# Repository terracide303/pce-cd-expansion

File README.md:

# PC Engine CD-ROM² card

> **Beta.** The PCB design is done, nothing has been built or tested yet. The FPGA core
> is still in development and will not be public until it is done.

A HuCard-sized card for the PC Engine / TurboGrafx-16. It plugs into the
**HuCard slot** and emulates the CD-ROM² system from a microSD card. No
expansion-port hardware and no CD unit are needed.

## On the card

- Lattice ECP5-45F FPGA with SDRAM and config flash (core section after the Icepi Zero)
- RP2040 companion and microSD
- Two USB-C ports: FPGA programming (FT231X) and the RP2040
- PCM5102A audio DAC: a stereo 3.5 mm jack, plus mono to the console
- 5 V bus translators at the card edge
- 4 layers, 54.1 × 85.4 mm, 1.6 mm, ENIG gold fingers

## Status

| part | state |
|---|---|
| schematic | done, checked |
| PCB | done, beta |
| FPGA core | in development, not public yet |
| ordered / tested | no |

## Layout

- `hw/card/`: KiCad project
- `tools/`: scripts that generate, check and lay out the board, and make the fab files
- `docs/`: [the card](docs/CARD.md), [how it is built](docs/WORKFLOW.md), [ordering](docs/ORDER.md); old notes in `docs/archive/`

## Credits

- [Icepi Zero](https://github.com/cheyao/icepi-zero) (Solderpad 2.1): the FPGA core section of the board
- [MiSTer TurboGrafx-16 core](https://github.com/MiSTer-devel/TurboGrafx16_MiSTer): reference for the CD hardware
- [HuCARD-repro](https://github.com/partlyhuman/HuCARD-repro): HuCard dimensions

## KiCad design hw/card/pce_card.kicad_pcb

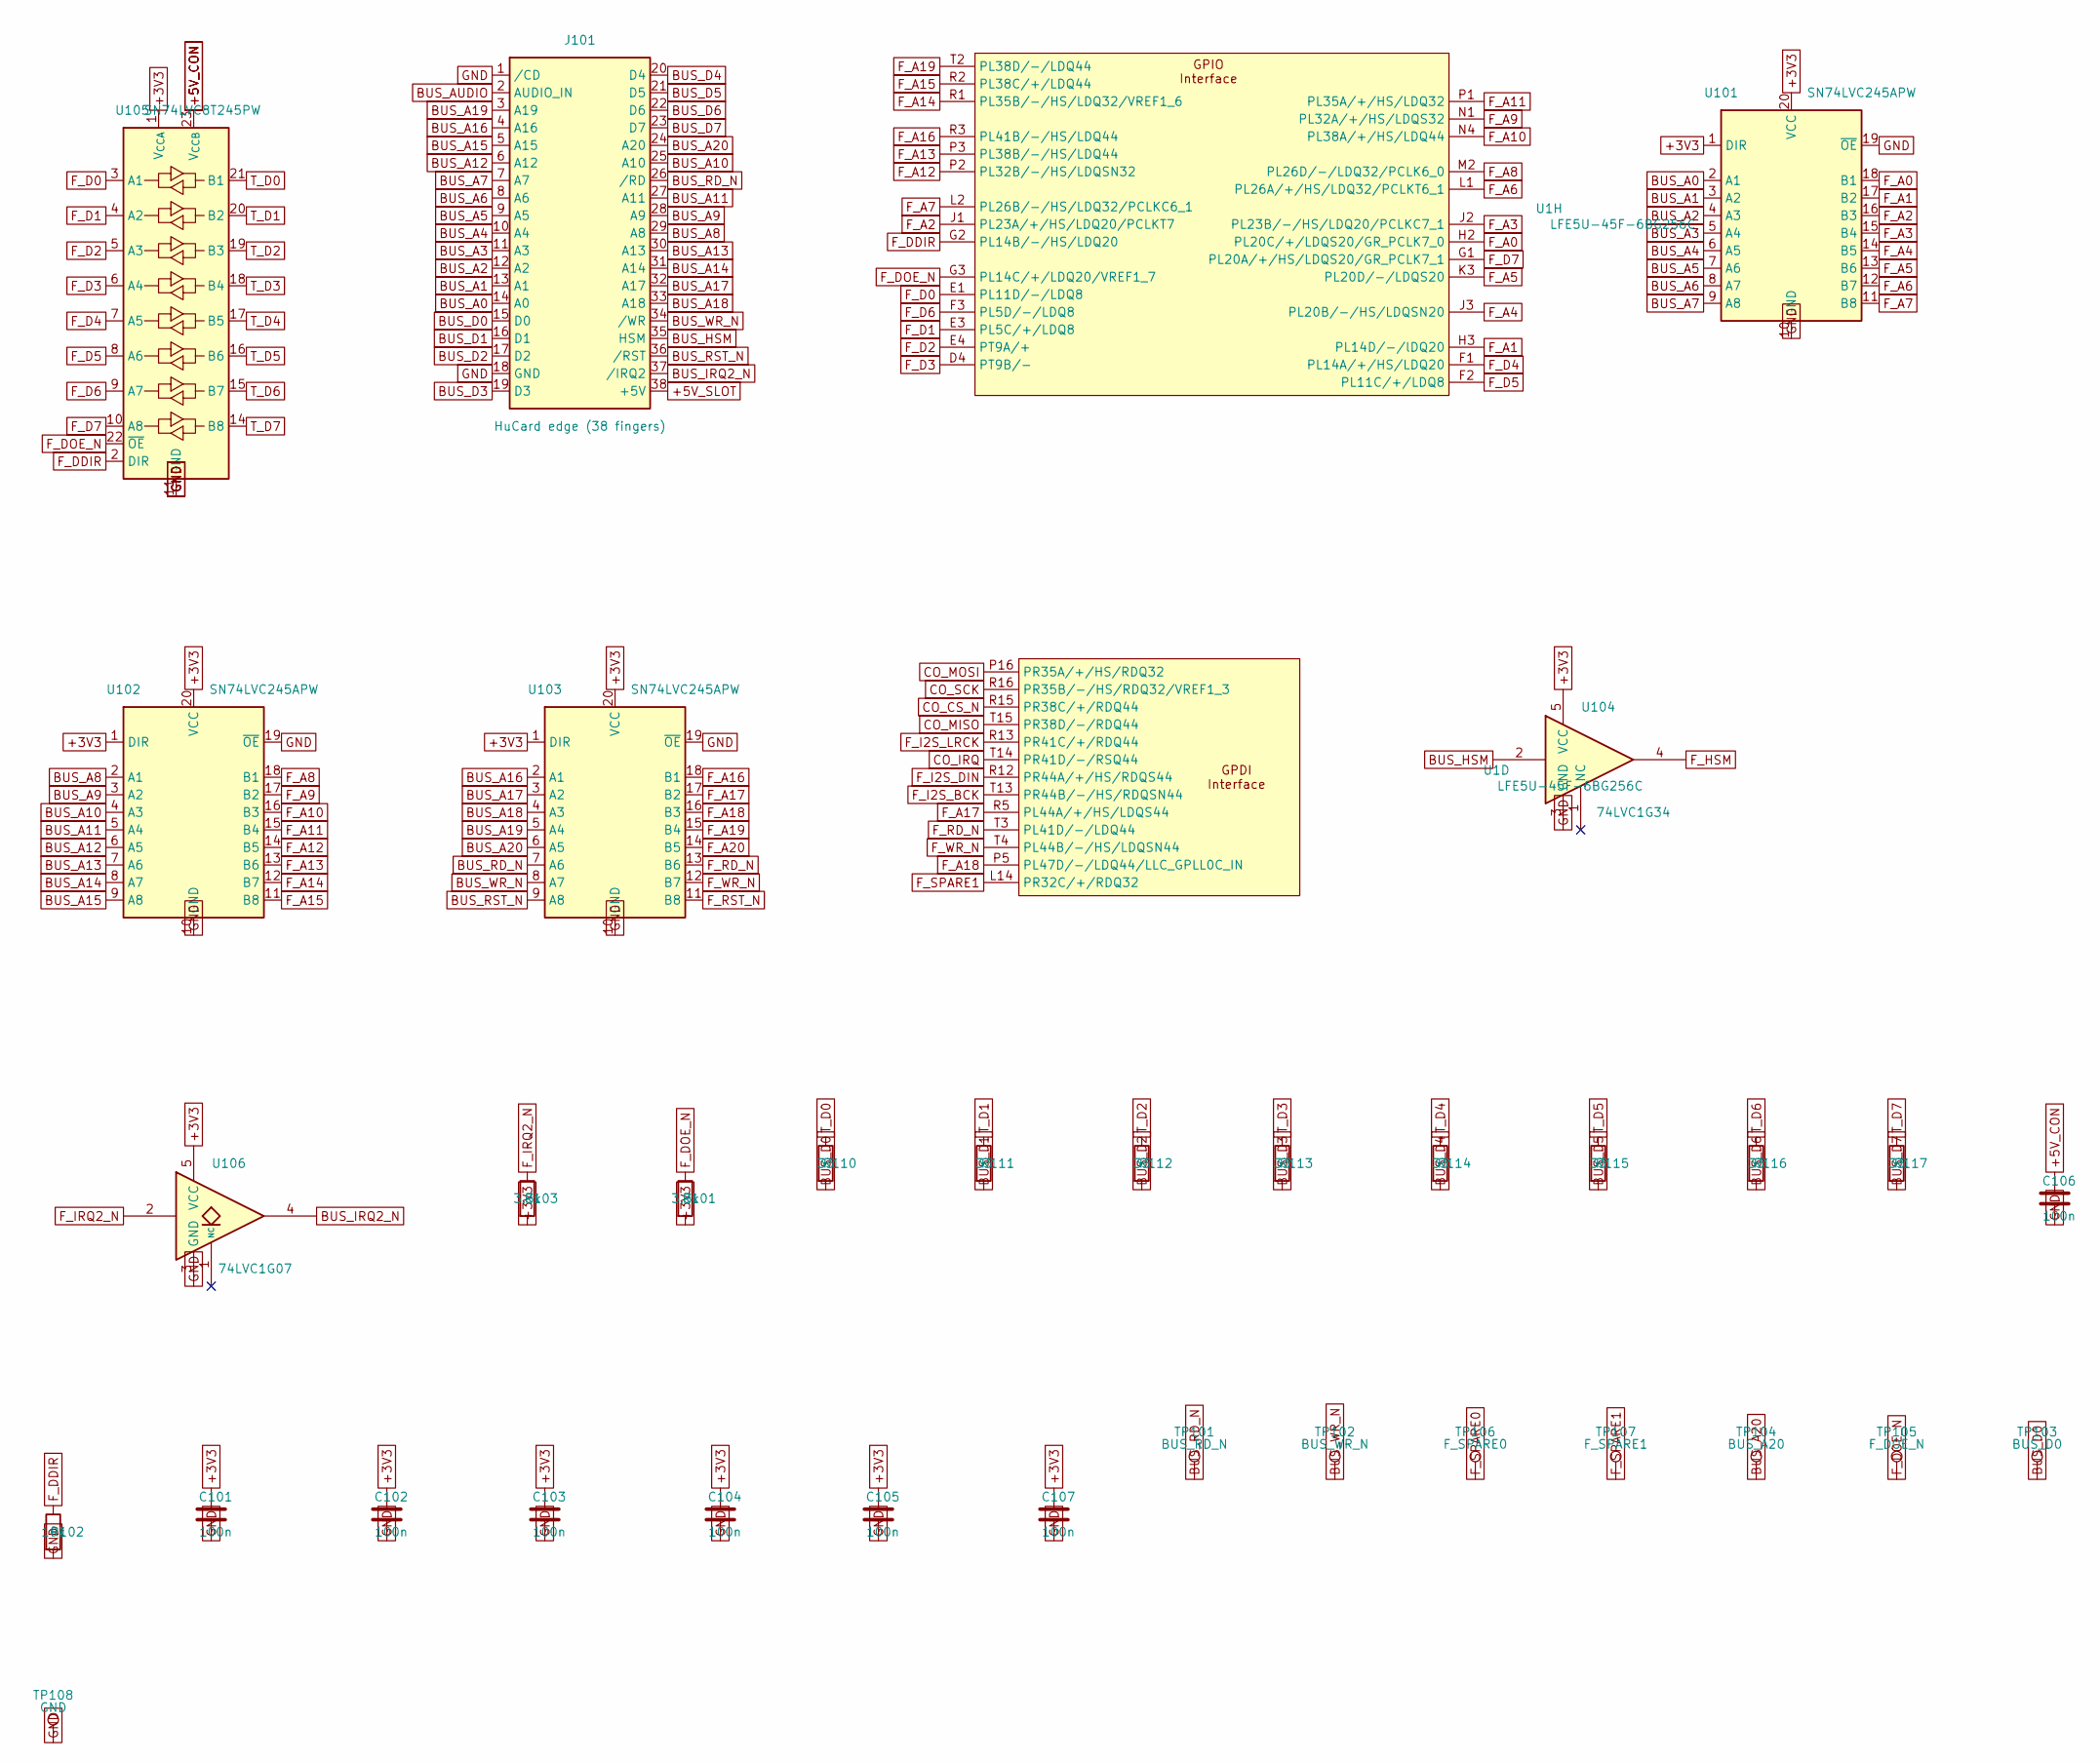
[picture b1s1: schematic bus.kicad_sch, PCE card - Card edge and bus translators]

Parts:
C101, C102, C103, C104, C105, C106, C107: 100n; C_0402_1005Metric; LCSC C307331
J101: HuCard edge (38 fingers); HuCard_Edge_38
R101, R103: 3.3k; R_0402_1005Metric; LCSC C25890
R102: 10k; R_0402_1005Metric; LCSC C25744
R110, R111, R112, R113, R114, R115, R116, R117: 33; R_0402_1005Metric
TP101: BUS_RD_N; TestPoint_Pad_D1.0mm
TP102: BUS_WR_N; TestPoint_Pad_D1.0mm
TP103: BUS_D0; TestPoint_Pad_D1.0mm
TP104: BUS_A20; TestPoint_Pad_D1.0mm
TP105: F_DOE_N; TestPoint_Pad_D1.0mm
TP106: F_SPARE0; TestPoint_Pad_D1.0mm
TP107: F_SPARE1; TestPoint_Pad_D1.0mm
TP108: GND; TestPoint_Pad_D1.0mm
U1: LFE5U-45F-6BG256C; BGA-256_14.0x14.0mm_Layout16x16_P0.8mm_Ball0.45mm_Pad0.32mm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; LCSC C1550834
U101, U102, U103: SN74LVC245APW; TSSOP-20_4.4x6.5mm_P0.65mm
U104: 74LVC1G34; SOT-23-5
U105: SN74LVC8T245PW; TSSOP-24_4.4x7.8mm_P0.65mm
U106: 74LVC1G07; SOT-23-5

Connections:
+3V3: C101.1, C102.1, C103.1, C104.1, C105.1, C107.1, R101.2, R103.2, U101.1 (DIR), U101.20 (VCC), U102.1 (DIR), U102.20 (VCC), U103.1 (DIR), U103.20 (VCC), U104.5 (VCC), U105.1 (V_{CCA}), U106.5 (VCC); also elsewhere on the board
+5V_CON: C106.1, U105.23 (V_{CCB}), U105.24 (V_{CCB}); also elsewhere on the board
+5V_SLOT: J101.38 (+5V); also elsewhere on the board
BUS_A0: J101.14 (A0), U101.2 (A1)
BUS_A1: J101.13 (A1), U101.3 (A2)
BUS_A2: J101.12 (A2), U101.4 (A3)
BUS_A3: J101.11 (A3), U101.5 (A4)
BUS_A4: J101.10 (A4), U101.6 (A5)
BUS_A5: J101.9 (A5), U101.7 (A6)
BUS_A6: J101.8 (A6), U101.8 (A7)
BUS_A7: J101.7 (A7), U101.9 (A8)
BUS_A8: J101.29 (A8), U102.2 (A1)
BUS_A9: J101.28 (A9), U102.3 (A2)
BUS_A10: J101.25 (A10), U102.4 (A3)
BUS_A11: J101.27 (A11), U102.5 (A4)
BUS_A12: J101.6 (A12), U102.6 (A5)
BUS_A13: J101.30 (A13), U102.7 (A6)
BUS_A14: J101.31 (A14), U102.8 (A7)
BUS_A15: J101.5 (A15), U102.9 (A8)
BUS_A16: J101.4 (A16), U103.2 (A1)
BUS_A17: J101.32 (A17), U103.3 (A2)
BUS_A18: J101.33 (A18), U103.4 (A3)
BUS_A19: J101.3 (A19), U103.5 (A4)
BUS_A20: J101.24 (A20), TP104.1, U103.6 (A5)
BUS_AUDIO: J101.2 (AUDIO_IN); also elsewhere on the board
BUS_D0: J101.15 (D0), R110.2, TP103.1
BUS_D1: J101.16 (D1), R111.2
BUS_D2: J101.17 (D2), R112.2
BUS_D3: J101.19 (D3), R113.2
BUS_D4: J101.20 (D4), R114.2
BUS_D5: J101.21 (D5), R115.2
BUS_D6: J101.22 (D6), R116.2
BUS_D7: J101.23 (D7), R117.2
BUS_HSM: J101.35 (HSM), U104.2
BUS_IRQ2_N: J101.37 (/IRQ2), U106.4
BUS_RD_N: J101.26 (/RD), TP101.1, U103.7 (A6)
BUS_RST_N: J101.36 (/RST), U103.9 (A8)
BUS_WR_N: J101.34 (/WR), TP102.1, U103.8 (A7)
CO_CS_N: U1.R15 (PR38C/+/RDQ44); also elsewhere on the board
CO_IRQ: U1.T14 (PR41D/-/RSQ44); also elsewhere on the board
CO_MISO: U1.T15 (PR38D/-/RDQ44); also elsewhere on the board
CO_MOSI: U1.P16 (PR35A/+/HS/RDQ32); also elsewhere on the board
CO_SCK: U1.R16 (PR35B/-/HS/RDQ32/VREF1_3); also elsewhere on the board
F_A0: U1.H2 (PL20C/+/LDQS20/GR_PCLK7_0), U101.18 (B1)
F_A1: U1.H3 (PL14D/-/lDQ20), U101.17 (B2)
F_A2: U1.J1 (PL23A/+/HS/LDQ20/PCLKT7), U101.16 (B3)
F_A3: U1.J2 (PL23B/-/HS/LDQ20/PCLKC7_1), U101.15 (B4)
F_A4: U1.J3 (PL20B/-/HS/LDQSN20), U101.14 (B5)
F_A5: U1.K3 (PL20D/-/LDQS20), U101.13 (B6)
F_A6: U1.L1 (PL26A/+/HS/LDQ32/PCLKT6_1), U101.12 (B7)
F_A7: U1.L2 (PL26B/-/HS/LDQ32/PCLKC6_1), U101.11 (B8)
F_A8: U1.M2 (PL26D/-/LDQ32/PCLK6_0), U102.18 (B1)
F_A9: U1.N1 (PL32A/+/HS/LDQS32), U102.17 (B2)
F_A10: U1.N4 (PL38A/+/HS/LDQ44), U102.16 (B3)
F_A11: U1.P1 (PL35A/+/HS/LDQ32), U102.15 (B4)
F_A12: U1.P2 (PL32B/-/HS/LDQSN32), U102.14 (B5)
F_A13: U1.P3 (PL38B/-/HS/LDQ44), U102.13 (B6)
F_A14: U1.R1 (PL35B/-/HS/LDQ32/VREF1_6), U102.12 (B7)
F_A15: U1.R2 (PL38C/+/LDQ44), U102.11 (B8)
F_A16: U1.R3 (PL41B/-/HS/LDQ44), U103.18 (B1)
F_A17: U1.R5 (PL44A/+/HS/LDQS44), U103.17 (B2)
F_A18: U1.P5 (PL47D/-/LDQ44/LLC_GPLL0C_IN), U103.16 (B3)
F_A19: U1.T2 (PL38D/-/LDQ44), U103.15 (B4)
F_A20: U103.14 (B5); also elsewhere on the board
F_D0: U1.E1 (PL11D/-/LDQ8), U105.3 (A1)
F_D1: U1.E3 (PL5C/+/LDQ8), U105.4 (A2)
F_D2: U1.E4 (PT9A/+), U105.5 (A3)
F_D3: U1.D4 (PT9B/-), U105.6 (A4)
F_D4: U1.F1 (PL14A/+/HS/LDQ20), U105.7 (A5)
F_D5: U1.F2 (PL11C/+/LDQ8), U105.8 (A6)
F_D6: U1.F3 (PL5D/-/LDQ8), U105.9 (A7)
F_D7: U1.G1 (PL20A/+/HS/LDQS20/GR_PCLK7_1), U105.10 (A8)
F_DDIR: R102.1, U1.G2 (PL14B/-/HS/LDQ20), U105.2 (DIR)
F_DOE_N: R101.1, TP105.1, U1.G3 (PL14C/+/LDQ20/VREF1_7), U105.22 (~OE)
F_HSM: U104.4; also elsewhere on the board
F_I2S_BCK: U1.T13 (PR44B/-/HS/RDQSN44); also elsewhere on the board
F_I2S_DIN: U1.R12 (PR44A/+/HS/RDQS44); also elsewhere on the board
F_I2S_LRCK: U1.R13 (PR41C/+/RDQ44); also elsewhere on the board
F_IRQ2_N: R103.1, U106.2; also elsewhere on the board
F_RD_N: U1.T3 (PL41D/-/LDQ44), U103.13 (B6)
F_RST_N: U103.11 (B8); also elsewhere on the board
F_SPARE0: TP106.1; also elsewhere on the board
F_SPARE1: TP107.1, U1.L14 (PR32C/+/RDQ32)
F_WR_N: U1.T4 (PL44B/-/HS/LDQSN44), U103.12 (B7)
GND: C101.2, C102.2, C103.2, C104.2, C105.2, C106.2, C107.2, J101.1 (/CD), J101.18 (GND), R102.2, TP108.1, U101.10 (GND), U101.19 (~OE), U102.10 (GND), U102.19 (~OE), U103.10 (GND), U103.19 (~OE), U104.3 (GND), U105.11 (GND), U105.12 (GND), U105.13 (GND), U106.3 (GND); also elsewhere on the board
T_D0: R110.1, U105.21 (B1)
T_D1: R111.1, U105.20 (B2)
T_D2: R112.1, U105.19 (B3)
T_D3: R113.1, U105.18 (B4)
T_D4: R114.1, U105.17 (B5)
T_D5: R115.1, U105.16 (B6)
T_D6: R116.1, U105.15 (B7)
T_D7: R117.1, U105.14 (B8)

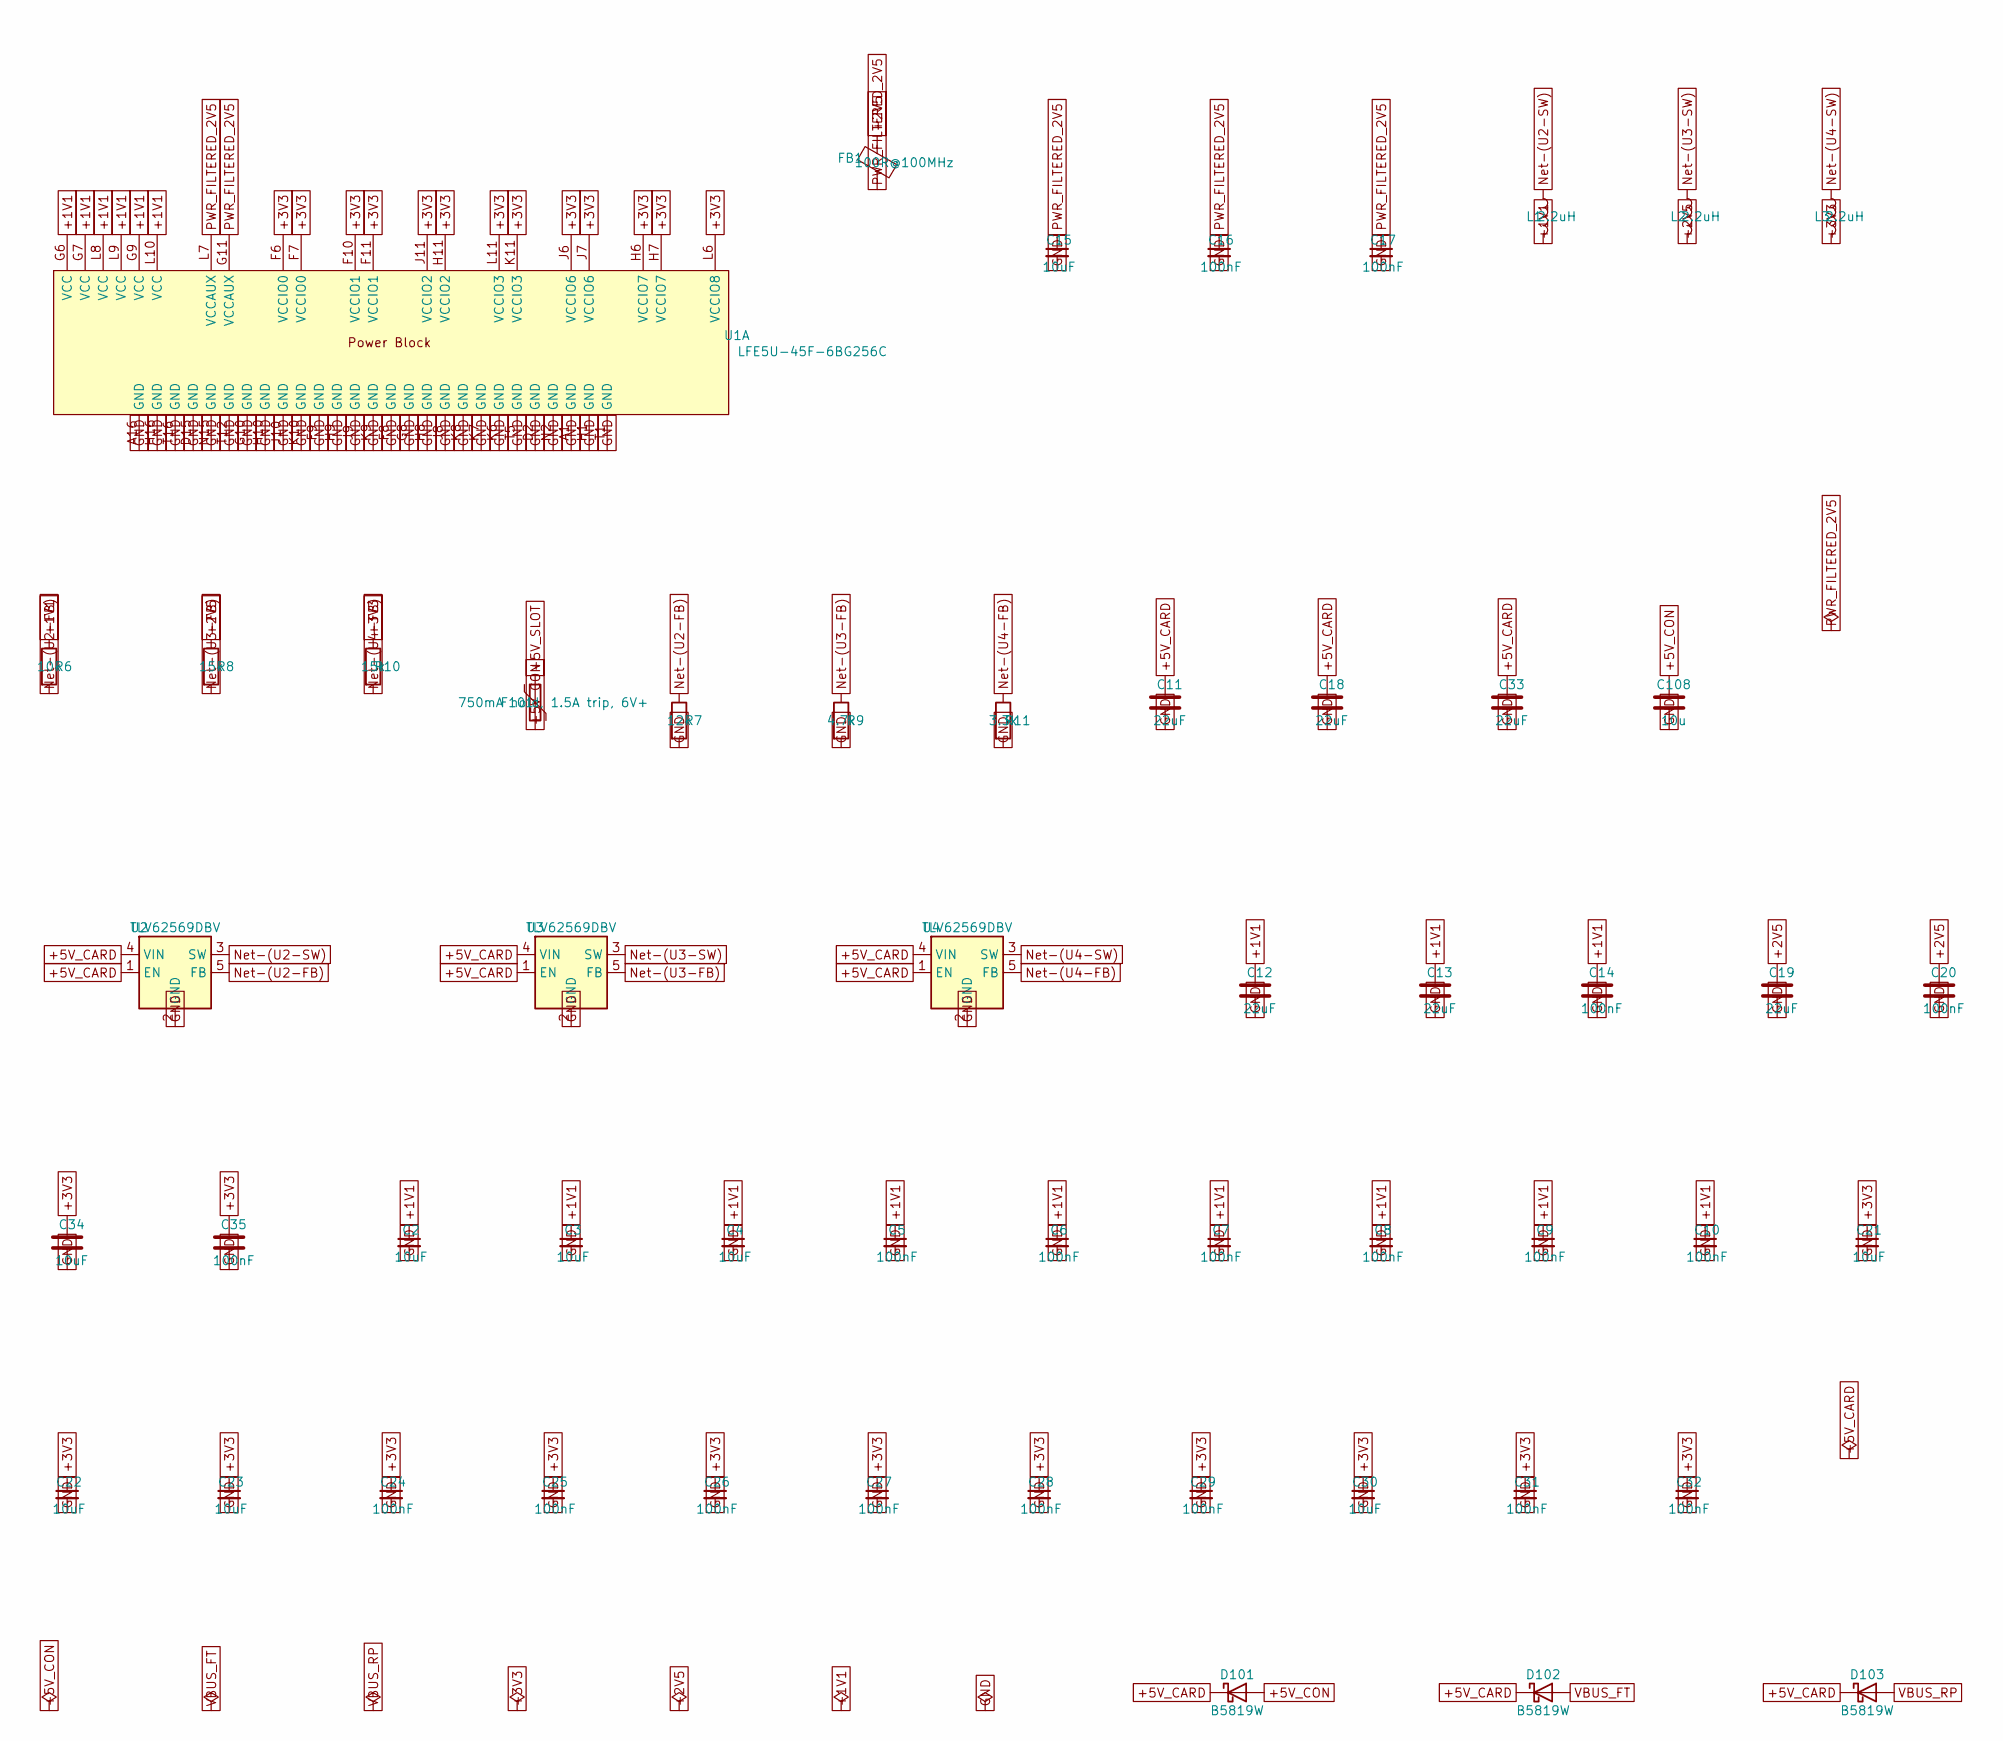
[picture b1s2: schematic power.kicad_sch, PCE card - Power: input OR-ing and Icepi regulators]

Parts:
C2, C3, C4, C15, C21, C22, C23, C30, C34: 10uF; C_0603_1608Metric; LCSC C19702
C5, C6, C7, C8, C9, C10, C14, C16, C17, C20, C24, C25, C26, C27, C28, C29, C31, C32, C35: 100nF; C_0402_1005Metric; LCSC C307331
C11, C12, C13, C18, C19, C33: 22uF; C_0603_1608Metric; LCSC C59461
C108: 10u; C_0603_1608Metric; LCSC C19702
D101, D102, D103: B5819W; D_SOD-123
F101: 750mA hold, 1.5A trip, 6V+; Fuse_1206_3216Metric
FB1: 100R@100MHz; L_0805_2012Metric; LCSC C74480
L1, L2, L3: 2.2uH; L_0805_2012Metric; LCSC C107322
R6: 10k; R_0402_1005Metric; LCSC C25744
R7: 12k; R_0402_1005Metric; LCSC C25752
R8, R10: 15k; R_0402_1005Metric; LCSC C25756
R9: 4.7k; R_0402_1005Metric; LCSC C25900
R11: 3.3k; R_0402_1005Metric; LCSC C25890
U1: LFE5U-45F-6BG256C; BGA-256_14.0x14.0mm_Layout16x16_P0.8mm_Ball0.45mm_Pad0.32mm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; LCSC C1550834
U2, U3, U4: TLV62569DBV; SOT-23-5; LCSC C141836

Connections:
+1V1: C2.1, C3.1, C4.1, C5.1, C6.1, C7.1, C8.1, C9.1, C10.1, C12.1, C13.1, C14.1, L1.2, R6.1, U1.G6 (VCC), U1.G7 (VCC), U1.G9 (VCC), U1.L8 (VCC), U1.L9 (VCC), U1.L10 (VCC); also elsewhere on the board
+2V5: C19.1, C20.1, FB1.1, L2.2, R8.1; also elsewhere on the board
+3V3: C21.1, C22.1, C23.1, C24.1, C25.1, C26.1, C27.1, C28.1, C29.1, C30.1, C31.1, C32.1, C34.1, C35.1, L3.2, R10.1, U1.F6 (VCCIO0), U1.F7 (VCCIO0), U1.F10 (VCCIO1), U1.F11 (VCCIO1), U1.H6 (VCCIO7), U1.H7 (VCCIO7), U1.H11 (VCCIO2), U1.J6 (VCCIO6), U1.J7 (VCCIO6), U1.J11 (VCCIO2), U1.K11 (VCCIO3), U1.L6 (VCCIO8), U1.L11 (VCCIO3); also elsewhere on the board
+5V_CARD: C11.1, C18.1, C33.1, D101.1 (K), D102.1 (K), D103.1 (K), U2.1 (EN), U2.4 (VIN), U3.1 (EN), U3.4 (VIN), U4.1 (EN), U4.4 (VIN); also elsewhere on the board
+5V_CON: C108.1, D101.2 (A), F101.2; also elsewhere on the board
+5V_SLOT: F101.1; also elsewhere on the board
GND: C2.2, C3.2, C4.2, C5.2, C6.2, C7.2, C8.2, C9.2, C10.2, C11.2, C12.2, C13.2, C14.2, C15.2, C16.2, C17.2, C18.2, C19.2, C20.2, C21.2, C22.2, C23.2, C24.2, C25.2, C26.2, C27.2, C28.2, C29.2, C30.2, C31.2, C32.2, C33.2, C34.2, C35.2, C108.2, R7.2, R9.2, R11.2, U1.A1 (GND), U1.A16 (GND), U1.D2 (GND), U1.D15 (GND), U1.F8 (GND), U1.F9 (GND), U1.G8 (GND), U1.G10 (GND), U1.H1 (GND), U1.H8 (GND), U1.H9 (GND), U1.H10 (GND), U1.H16 (GND), U1.J8 (GND), U1.J9 (GND), U1.J10 (GND), U1.K6 (GND), U1.K7 (GND), U1.K8 (GND), U1.K9 (GND), U1.K10 (GND), U1.N2 (GND), U1.N15 (GND), U1.T1 (GND), U1.T5 (GND), U1.T12 (GND), U1.T16 (GND), U2.2 (GND), U3.2 (GND), U4.2 (GND); also elsewhere on the board
unnamed: R6.2, R7.1, U2.5 (FB)
unnamed: L1.1, U2.3 (SW)
unnamed: R8.2, R9.1, U3.5 (FB)
unnamed: L2.1, U3.3 (SW)
unnamed: R10.2, R11.1, U4.5 (FB)
unnamed: L3.1, U4.3 (SW)
PWR_FILTERED_2V5: C15.1, C16.1, C17.1, FB1.2, U1.G11 (VCCAUX), U1.L7 (VCCAUX)
VBUS_FT: D102.2 (A); also elsewhere on the board
VBUS_RP: D103.2 (A); also elsewhere on the board

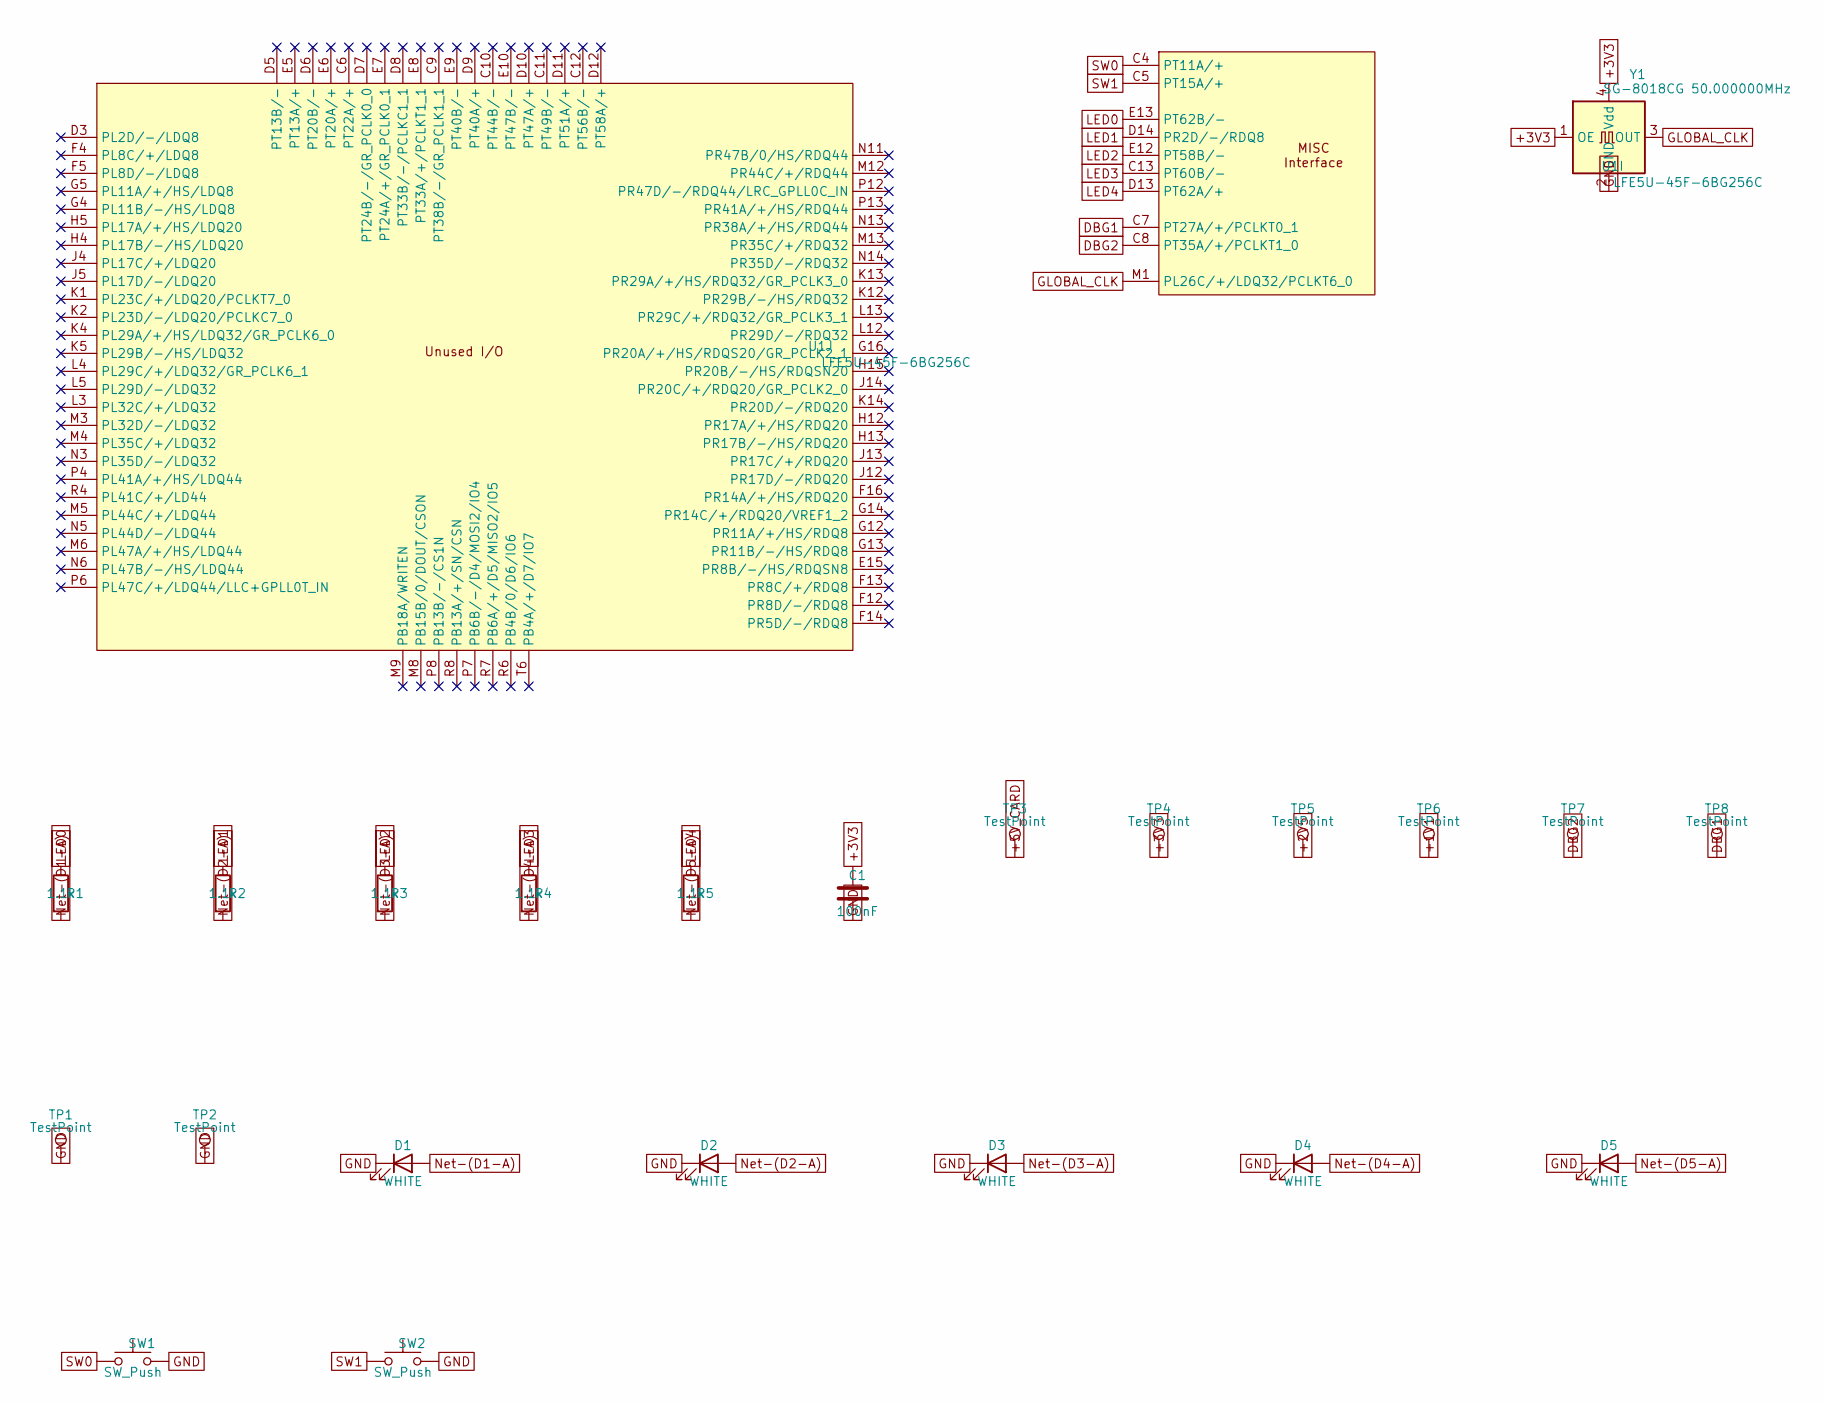
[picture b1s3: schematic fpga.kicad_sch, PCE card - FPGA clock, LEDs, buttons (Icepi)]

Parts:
C1: 100nF; C_0402_1005Metric; LCSC C307331
D1, D2, D3, D4, D5: WHITE; LED_0603_1608Metric; LCSC C2290
R1, R2, R3, R4, R5: 1.1k; R_0402_1005Metric; LCSC C140223
SW1, SW2: SW_Push; switch_button_TS-1088-AR02016; LCSC C720477
TP1, TP2, TP3, TP4, TP5, TP6: TestPoint; TestPoint_Pad_D2.0mm_Blank
TP7, TP8: TestPoint; TestPoint_Pad_D1.0mm_Blank
U1: LFE5U-45F-6BG256C; BGA-256_14.0x14.0mm_Layout16x16_P0.8mm_Ball0.45mm_Pad0.32mm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; LCSC C1550834
Y1: SG-8018CG 50.000000MHz; Oscillator_SMD_SiT_PQFN-4Pin_2.5x2.0mm; LCSC C390526

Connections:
+1V1: TP6.1; also elsewhere on the board
+2V5: TP5.1; also elsewhere on the board
+3V3: C1.1, TP4.1, Y1.1 (OE), Y1.4 (Vdd); also elsewhere on the board
+5V_CARD: TP3.1; also elsewhere on the board
DBG1: TP8.1, U1.C7 (PT27A/+/PCLKT0_1)
DBG2: TP7.1, U1.C8 (PT35A/+/PCLKT1_0)
GLOBAL_CLK: U1.M1 (PL26C/+/LDQ32/PCLKT6_0), Y1.3 (OUT)
GND: C1.2, D1.1 (K), D2.1 (K), D3.1 (K), D4.1 (K), D5.1 (K), SW1.2, SW2.2, TP1.1, TP2.1, Y1.2 (GND); also elsewhere on the board
LED0: R1.1, U1.E13 (PT62B/-)
LED1: R2.1, U1.D14 (PR2D/-/RDQ8)
LED2: R3.1, U1.E12 (PT58B/-)
LED3: R4.1, U1.C13 (PT60B/-)
LED4: R5.1, U1.D13 (PT62A/+)
unnamed: D1.2 (A), R1.2
unnamed: D2.2 (A), R2.2
unnamed: D3.2 (A), R3.2
unnamed: D4.2 (A), R4.2
unnamed: D5.2 (A), R5.2
SW0: SW1.1, U1.C4 (PT11A/+)
SW1: SW2.1, U1.C5 (PT15A/+)

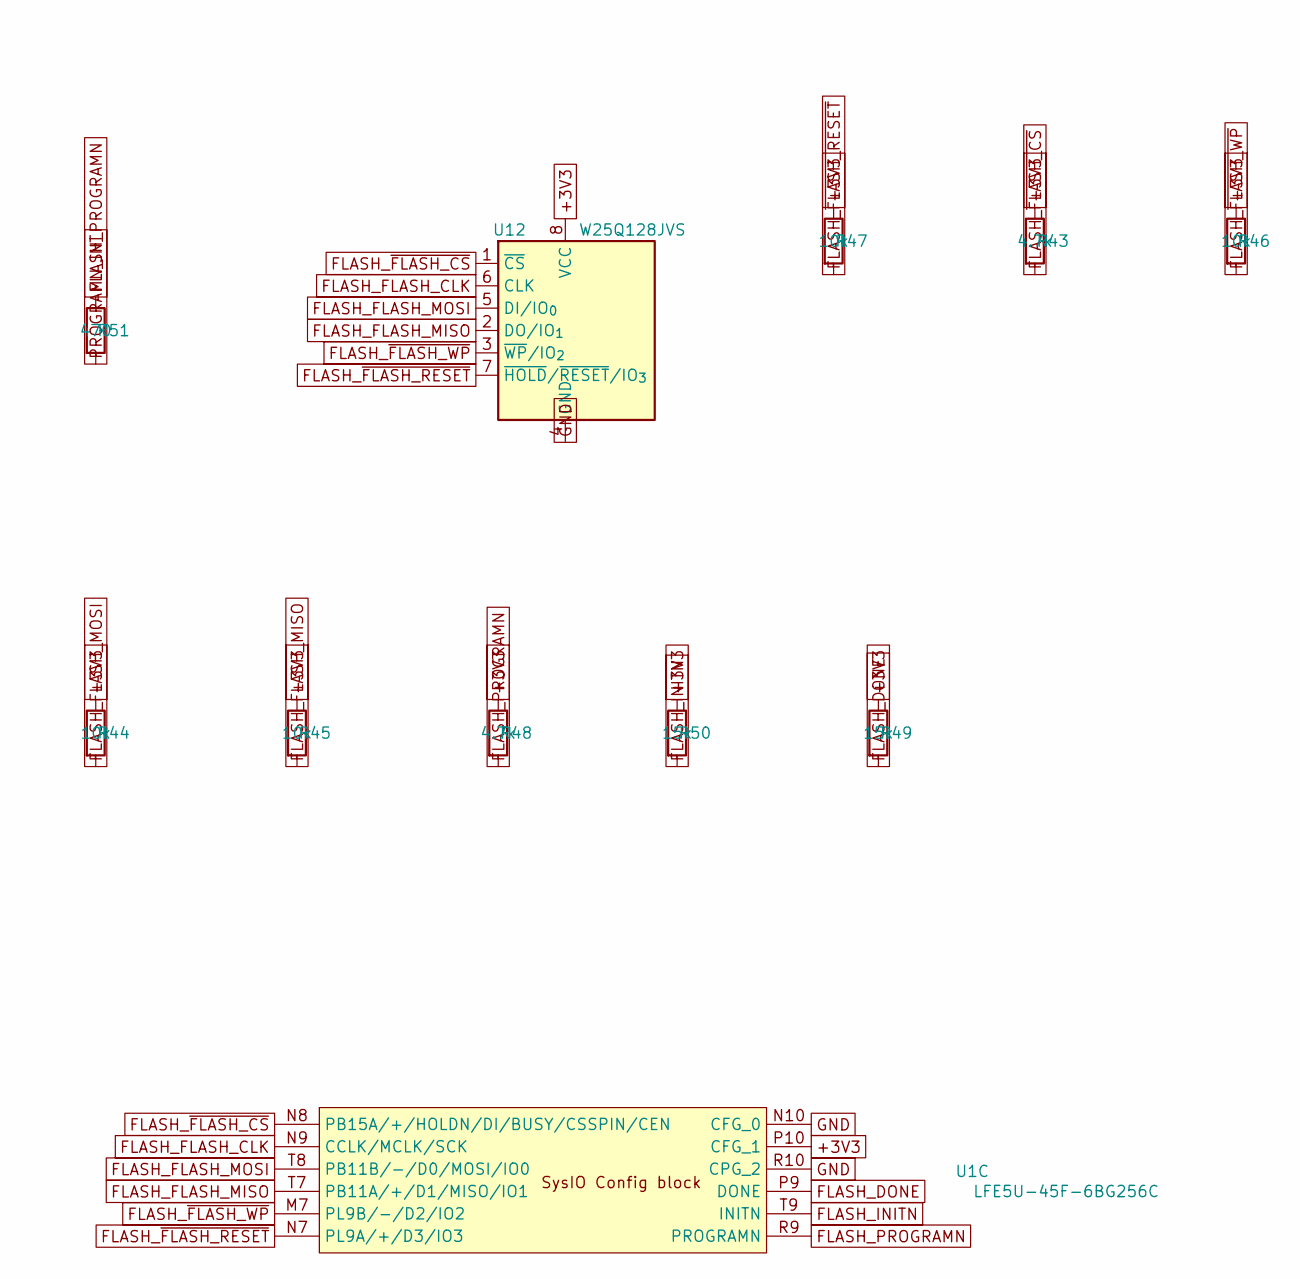
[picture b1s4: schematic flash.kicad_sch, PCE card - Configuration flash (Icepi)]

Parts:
R43: 4.7k; R_0402_1005Metric; LCSC C25900
R44, R45, R46, R47: 10k; R_0402_1005Metric; LCSC C25744
R48: 4.7k; R_0402_1005Metric; LCSC C25756
R49, R50: 15k; R_0402_1005Metric; LCSC C25756
R51: 470; R_0402_1005Metric; LCSC C25117
U1: LFE5U-45F-6BG256C; BGA-256_14.0x14.0mm_Layout16x16_P0.8mm_Ball0.45mm_Pad0.32mm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; LCSC C1550834
U12: W25Q128JVS; SOIC-8_5.3x5.3mm_P1.27mm; LCSC C97521

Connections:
+3V3: R43.1, R44.1, R45.1, R46.1, R47.1, R48.1, R49.1, R50.1, U1.P10 (CFG_1), U12.8 (VCC); also elsewhere on the board
FLASH_DONE: R49.2, U1.P9 (DONE)
FLASH_FLASH_CLK: U1.N9 (CCLK/MCLK/SCK), U12.6 (CLK)
FLASH_FLASH_MISO: R45.2, U1.T7 (PB11A/+/D1/MISO/IO1), U12.2 (DO/IO_{1})
FLASH_FLASH_MOSI: R44.2, U1.T8 (PB11B/-/D0/MOSI/IO0), U12.5 (DI/IO_{0})
FLASH_INITN: R50.2, U1.T9 (INITN)
FLASH_PROGRAMN: R48.2, R51.1, U1.R9 (PROGRAMN)
FLASH_~FLASH_CS: R43.2, U1.N8 (PB15A/+/HOLDN/DI/BUSY/CSSPIN/CEN), U12.1 (~CS)
FLASH_~FLASH_RESET: R47.2, U1.N7 (PL9A/+/D3/IO3), U12.7 (~HOLD/~RESET/IO_{3})
FLASH_~FLASH_WP: R46.2, U1.M7 (PL9B/-/D2/IO2), U12.3 (~WP/IO_{2})
GND: U1.N10 (CFG_0), U1.R10 (CPG_2), U12.4 (GND); also elsewhere on the board
PROGRAMN_INT: R51.2; also elsewhere on the board

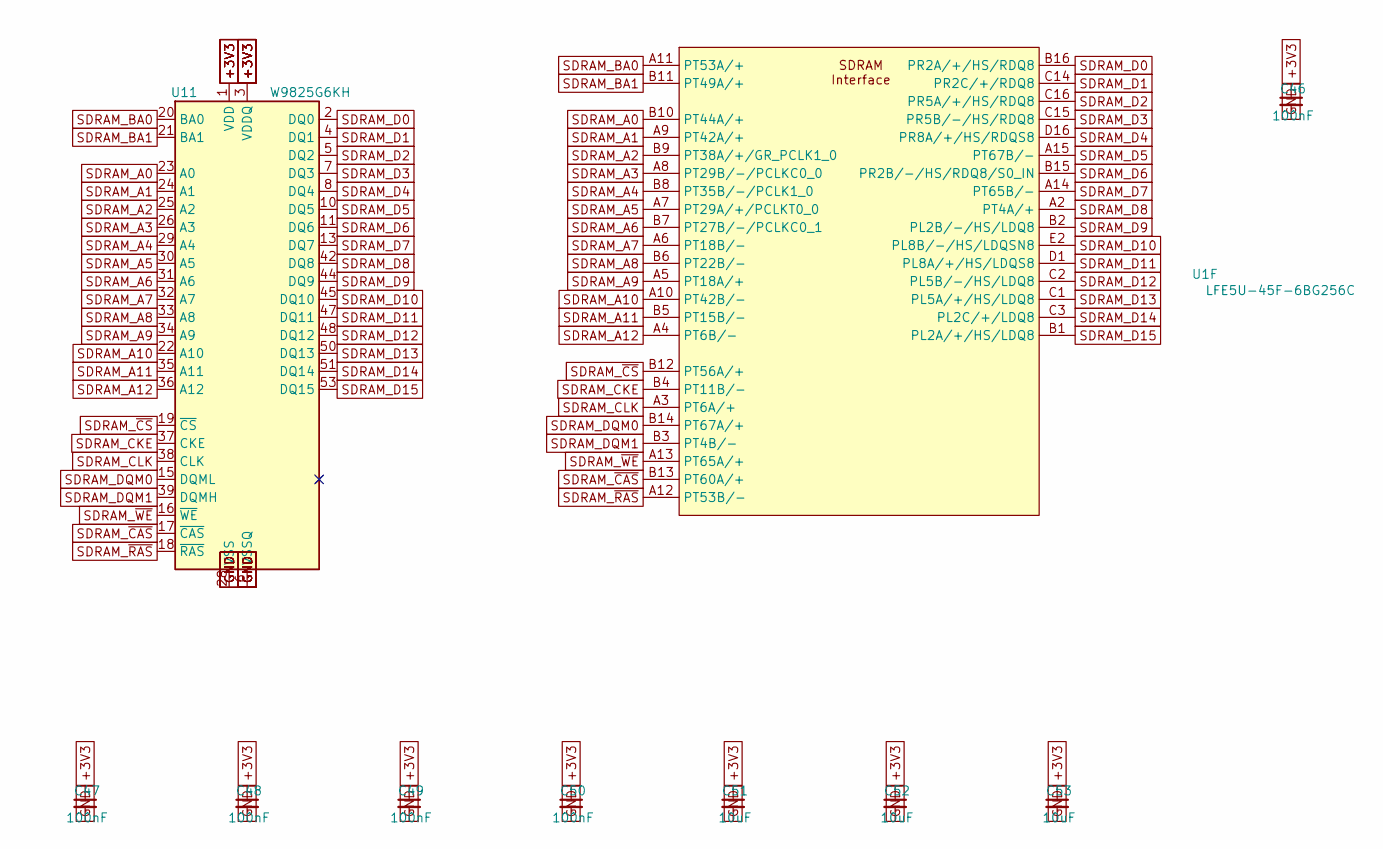
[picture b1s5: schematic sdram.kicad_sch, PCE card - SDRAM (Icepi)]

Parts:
C46, C47, C48, C49, C50: 100nF; C_0402_1005Metric; LCSC C307331
C51, C52, C53: 10uF; C_0603_1608Metric; LCSC C19702
U1: LFE5U-45F-6BG256C; BGA-256_14.0x14.0mm_Layout16x16_P0.8mm_Ball0.45mm_Pad0.32mm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; LCSC C1550834
U11: W9825G6KH; TSOP-II-54_22.2x10.16mm_P0.8mm; LCSC C62246

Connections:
+3V3: C46.1, C47.1, C48.1, C49.1, C50.1, C51.1, C52.1, C53.1, U11.1 (VDD), U11.3 (VDDQ), U11.9 (VDDQ), U11.14 (VDD), U11.27 (VDD), U11.43 (VDDQ), U11.49 (VDDQ); also elsewhere on the board
GND: C46.2, C47.2, C48.2, C49.2, C50.2, C51.2, C52.2, C53.2, U11.6 (VSSQ), U11.12 (VSSQ), U11.28 (VSS), U11.41 (VSS), U11.46 (VSSQ), U11.52 (VSSQ), U11.54 (VSS); also elsewhere on the board
SDRAM_A0: U1.B10 (PT44A/+), U11.23 (A0)
SDRAM_A1: U1.A9 (PT42A/+), U11.24 (A1)
SDRAM_A2: U1.B9 (PT38A/+/GR_PCLK1_0), U11.25 (A2)
SDRAM_A3: U1.A8 (PT29B/-/PCLKC0_0), U11.26 (A3)
SDRAM_A4: U1.B8 (PT35B/-/PCLK1_0), U11.29 (A4)
SDRAM_A5: U1.A7 (PT29A/+/PCLKT0_0), U11.30 (A5)
SDRAM_A6: U1.B7 (PT27B/-/PCLKC0_1), U11.31 (A6)
SDRAM_A7: U1.A6 (PT18B/-), U11.32 (A7)
SDRAM_A8: U1.B6 (PT22B/-), U11.33 (A8)
SDRAM_A9: U1.A5 (PT18A/+), U11.34 (A9)
SDRAM_A10: U1.A10 (PT42B/-), U11.22 (A10)
SDRAM_A11: U1.B5 (PT15B/-), U11.35 (A11)
SDRAM_A12: U1.A4 (PT6B/-), U11.36 (A12)
SDRAM_BA0: U1.A11 (PT53A/+), U11.20 (BA0)
SDRAM_BA1: U1.B11 (PT49A/+), U11.21 (BA1)
SDRAM_CKE: U1.B4 (PT11B/-), U11.37 (CKE)
SDRAM_CLK: U1.A3 (PT6A/+), U11.38 (CLK)
SDRAM_D0: U1.B16 (PR2A/+/HS/RDQ8), U11.2 (DQ0)
SDRAM_D1: U1.C14 (PR2C/+/RDQ8), U11.4 (DQ1)
SDRAM_D2: U1.C16 (PR5A/+/HS/RDQ8), U11.5 (DQ2)
SDRAM_D3: U1.C15 (PR5B/-/HS/RDQ8), U11.7 (DQ3)
SDRAM_D4: U1.D16 (PR8A/+/HS/RDQS8), U11.8 (DQ4)
SDRAM_D5: U1.A15 (PT67B/-), U11.10 (DQ5)
SDRAM_D6: U1.B15 (PR2B/-/HS/RDQ8/S0_IN), U11.11 (DQ6)
SDRAM_D7: U1.A14 (PT65B/-), U11.13 (DQ7)
SDRAM_D8: U1.A2 (PT4A/+), U11.42 (DQ8)
SDRAM_D9: U1.B2 (PL2B/-/HS/LDQ8), U11.44 (DQ9)
SDRAM_D10: U1.E2 (PL8B/-/HS/LDQSN8), U11.45 (DQ10)
SDRAM_D11: U1.D1 (PL8A/+/HS/LDQS8), U11.47 (DQ11)
SDRAM_D12: U1.C2 (PL5B/-/HS/LDQ8), U11.48 (DQ12)
SDRAM_D13: U1.C1 (PL5A/+/HS/LDQ8), U11.50 (DQ13)
SDRAM_D14: U1.C3 (PL2C/+/LDQ8), U11.51 (DQ14)
SDRAM_D15: U1.B1 (PL2A/+/HS/LDQ8), U11.53 (DQ15)
SDRAM_DQM0: U1.B14 (PT67A/+), U11.15 (DQML)
SDRAM_DQM1: U1.B3 (PT4B/-), U11.39 (DQMH)
SDRAM_~CAS: U1.B13 (PT60A/+), U11.17 (~CAS)
SDRAM_~CS: U1.B12 (PT56A/+), U11.19 (~CS)
SDRAM_~RAS: U1.A12 (PT53B/-), U11.18 (~RAS)
SDRAM_~WE: U1.A13 (PT65A/+), U11.16 (~WE)

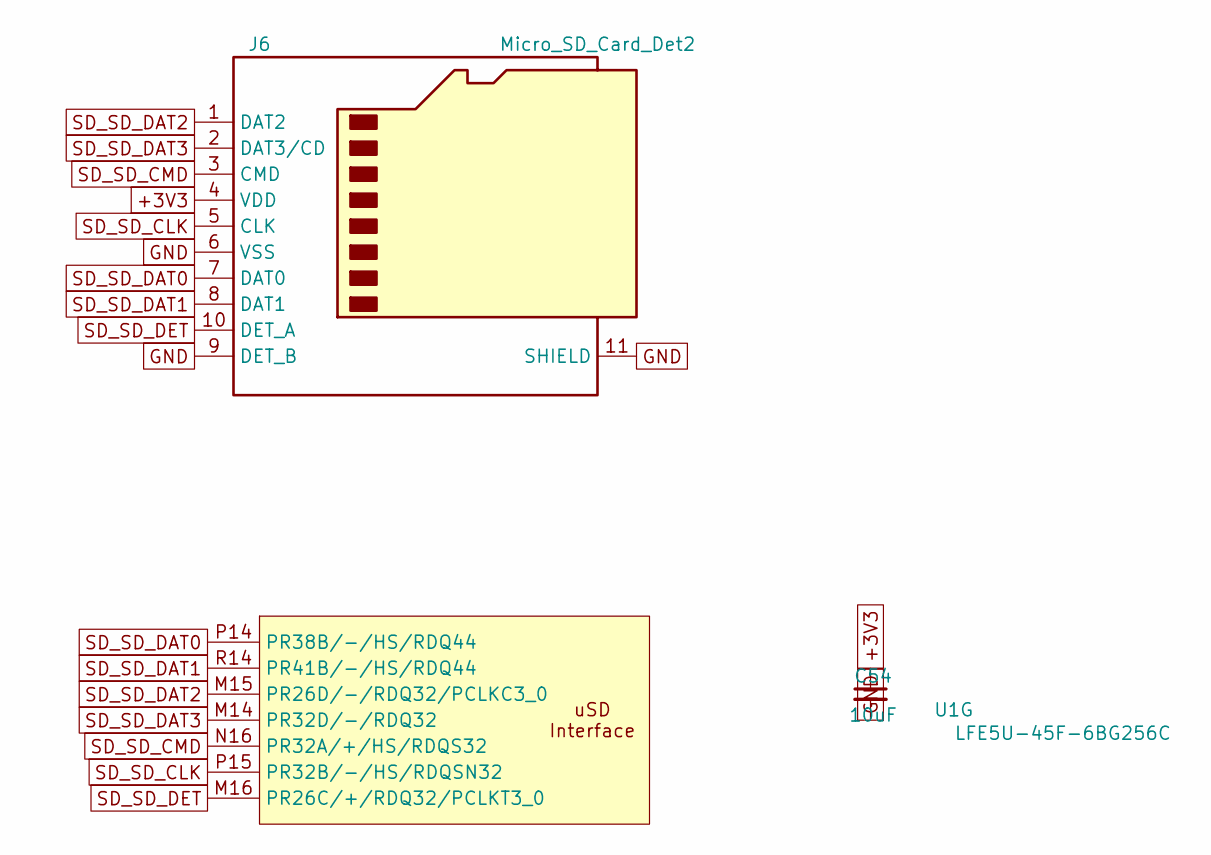
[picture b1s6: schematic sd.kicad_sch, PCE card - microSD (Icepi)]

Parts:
C54: 10uF; C_0603_1608Metric; LCSC C19702
J6: Micro_SD_Card_Det2; microSD_HC_SOFNG_TF-008; LCSC C428465
U1: LFE5U-45F-6BG256C; BGA-256_14.0x14.0mm_Layout16x16_P0.8mm_Ball0.45mm_Pad0.32mm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; LCSC C1550834

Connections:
+3V3: C54.1, J6.4 (VDD); also elsewhere on the board
GND: C54.2, J6.6 (VSS), J6.9 (DET_B), J6.11 (SHIELD); also elsewhere on the board
SD_SD_CLK: J6.5 (CLK), U1.P15 (PR32B/-/HS/RDQSN32)
SD_SD_CMD: J6.3 (CMD), U1.N16 (PR32A/+/HS/RDQS32)
SD_SD_DAT0: J6.7 (DAT0), U1.P14 (PR38B/-/HS/RDQ44)
SD_SD_DAT1: J6.8 (DAT1), U1.R14 (PR41B/-/HS/RDQ44)
SD_SD_DAT2: J6.1 (DAT2), U1.M15 (PR26D/-/RDQ32/PCLKC3_0)
SD_SD_DAT3: J6.2 (DAT3/CD), U1.M14 (PR32D/-/RDQ32)
SD_SD_DET: J6.10 (DET_A), U1.M16 (PR26C/+/RDQ32/PCLKT3_0)

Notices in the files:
hw/card/audio.kicad_sch:
FPGA core derived from Icepi Zero v1.4, (c) Chengyin Yao, Solderpad Hardware License v2.1
